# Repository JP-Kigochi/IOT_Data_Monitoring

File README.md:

# IOT Data Monitoring of Temperature and Humidity

This is a project encompassing mechanical design, PCB design, embedded programming and data cleaning and analysis. It portrays the knowledge and skills I have acquired in the field of internet of things as well as in data visualization and analysis

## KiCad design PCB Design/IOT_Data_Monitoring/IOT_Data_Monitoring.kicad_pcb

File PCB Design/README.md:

# PCB Design of the Arduino Circuit

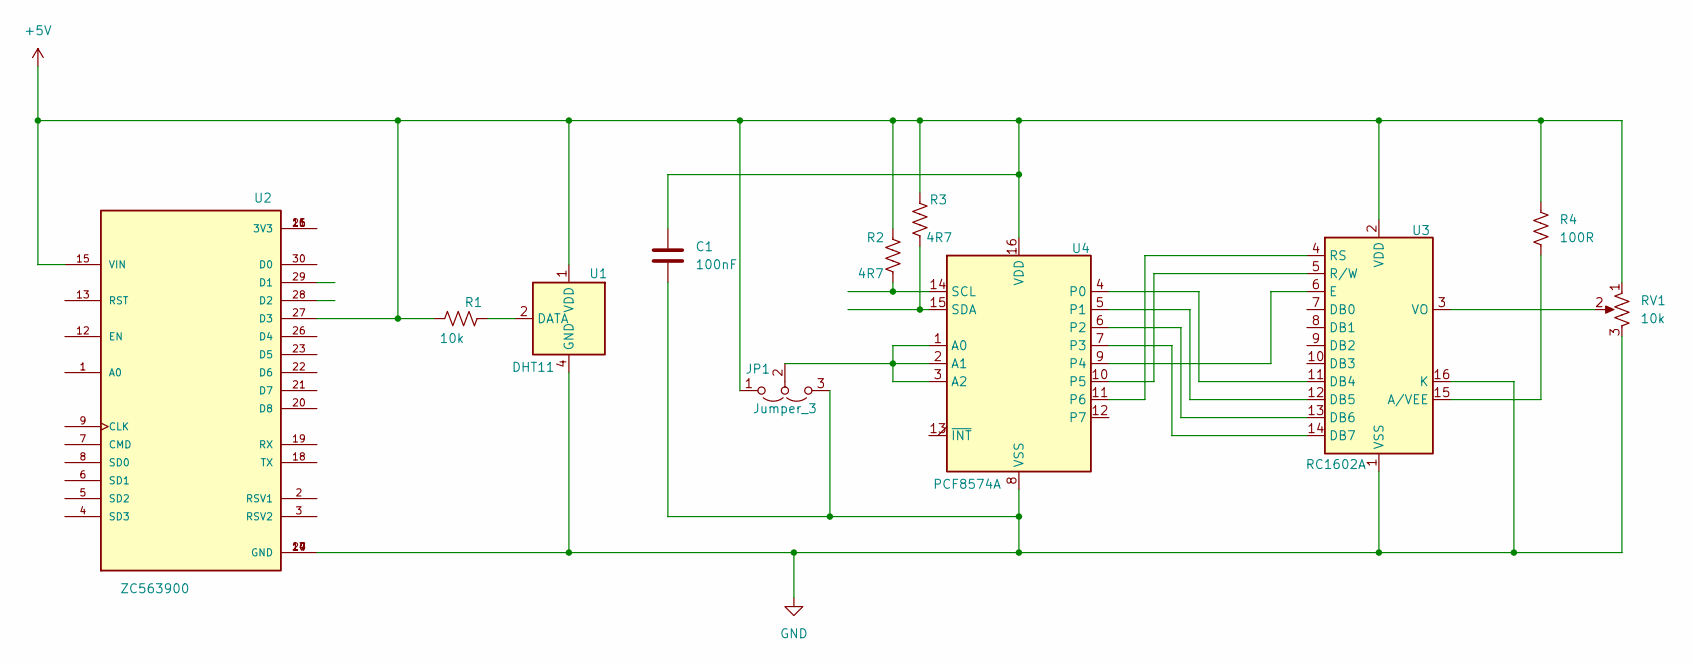
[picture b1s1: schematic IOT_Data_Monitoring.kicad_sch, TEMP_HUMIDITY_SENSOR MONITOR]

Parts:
C1: 100nF; CP_Radial_D5.0mm_P2.50mm
JP1: Jumper_3; SolderJumper-3_P1.3mm_Bridged2Bar12_RoundedPad1.0x1.5mm
R1: 10k; R_Axial_DIN0204_L3.6mm_D1.6mm_P5.08mm_Horizontal
R2, R3: 4R7; R_Axial_DIN0204_L3.6mm_D1.6mm_P5.08mm_Horizontal
R4: 100R; R_Axial_DIN0204_L3.6mm_D1.6mm_P5.08mm_Horizontal
RV1: 10k; Potentiometer_Bourns_3339P_Vertical_HandSoldering
U1: DHT11; Aosong_DHT11_5.5x12.0_P2.54mm
U2: ZC563900; MODULE_ZC563900; PARTREV 1.0
U3: RC1602A
U4: PCF8574A; SOIC-16_3.9x9.9mm_P1.27mm

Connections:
+5V: C1.1, JP1.1 (A), R1.1, R2.1, R3.1, R4.1, RV1.1, U1.1 (VDD), U2.15 (VIN), U2.27 (D3), U3.2 (VDD), U4.16 (VDD)
GND: C1.2, JP1.3 (B), RV1.3, U1.4 (GND), U2.10 (GND), U2.14 (GND), U2.17 (GND), U2.24 (GND), U3.1 (VSS), U3.16 (K), U4.8 (VSS)
unnamed: JP1.2 (C), U4.1 (A0), U4.2 (A1), U4.3 (A2)
unnamed: R1.2, U1.2 (DATA)
unnamed: U2.11 (3V3), U2.16 (3V3), U2.25 (3V3)
unnamed: R4.2, U3.15 (A/VEE)
unnamed: U3.11 (DB4), U4.4 (P0)
unnamed: U3.12 (DB5), U4.5 (P1)
unnamed: U3.13 (DB6), U4.6 (P2)
unnamed: U3.14 (DB7), U4.7 (P3)
unnamed: U3.6 (E), U4.9 (P4)
unnamed: U3.4 (RS), U4.11 (P6)
unnamed: U3.5 (R/W), U4.10 (P5)
unnamed: RV1.2, U3.3 (VO)
unnamed: R2.2, U4.14 (SCL)
unnamed: R3.2, U4.15 (SDA)

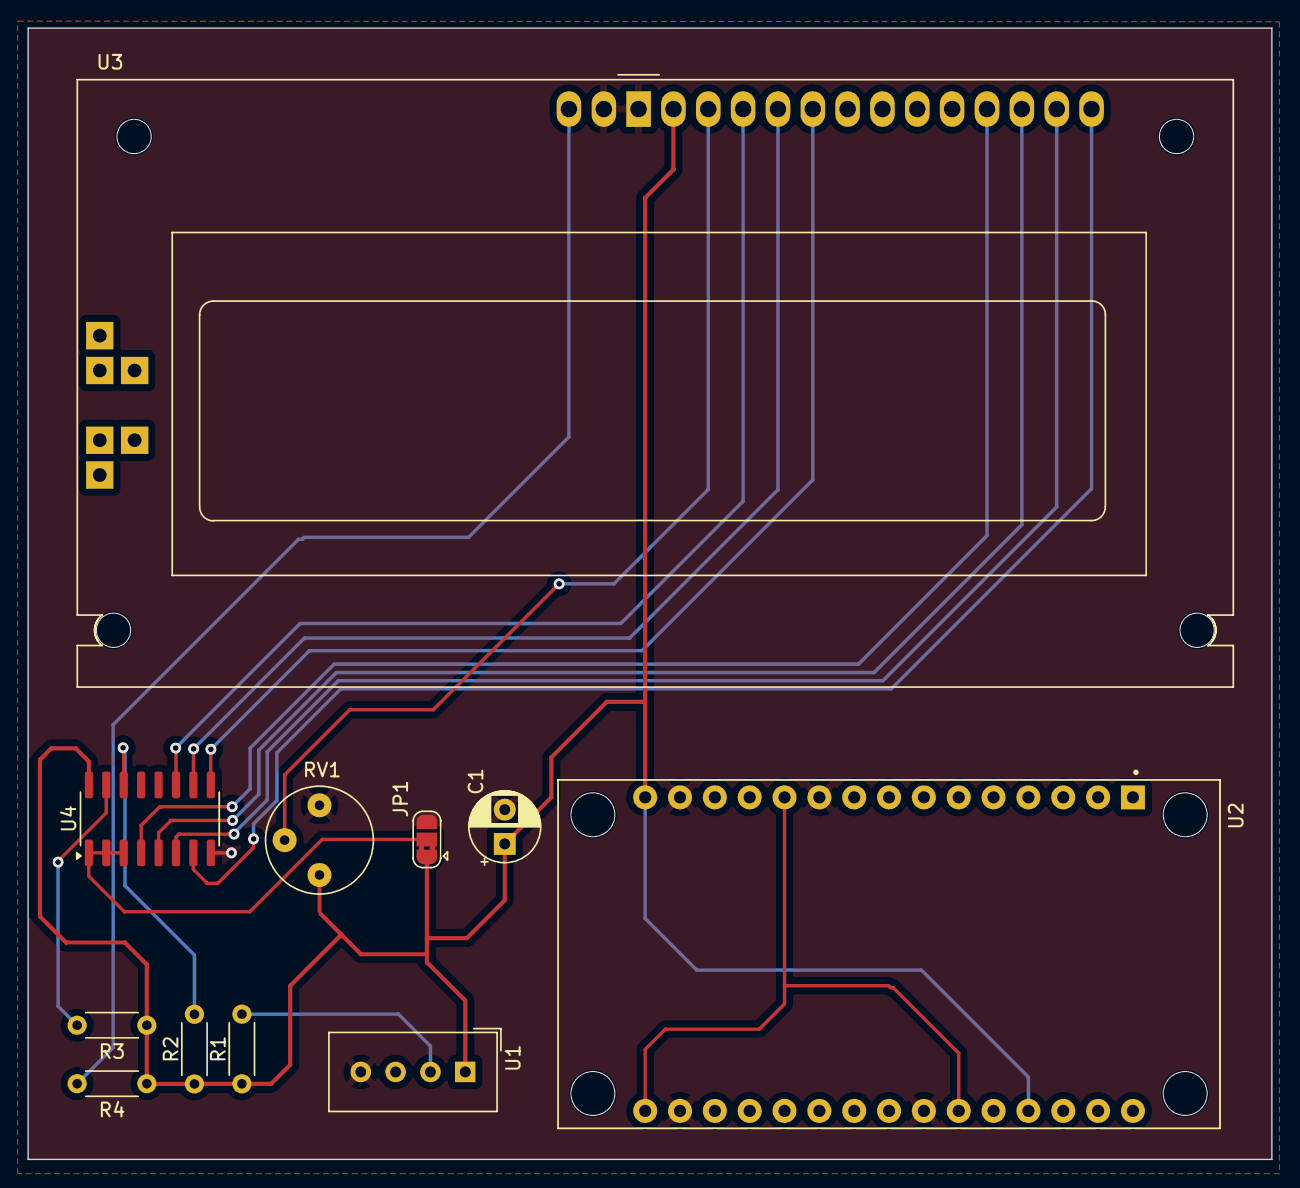
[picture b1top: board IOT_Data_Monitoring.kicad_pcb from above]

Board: 2 copper layers, 90.7 x 82.5 mm, 11 parts (0 on the bottom side), 16 nets.

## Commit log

2024-03-13 Add README
2024-03-13 Add Mechanical Design folder
2024-03-13 Add PCB design folder
2024-03-13 Add Project Schematic folder
2024-03-13 Add Data cleaning and analysis folder
2024-03-18 Add Arduino Uno fritz schematic
2024-03-18 Replace Arduino Uno with nodemcu esp8266 board
2024-03-18 Add arduino uno program
2024-03-18 Add nodemcu esp8266 board program integrating wifi
2024-03-19 Create kicad project schematic
2024-03-19 Create kicad project pcb layout
